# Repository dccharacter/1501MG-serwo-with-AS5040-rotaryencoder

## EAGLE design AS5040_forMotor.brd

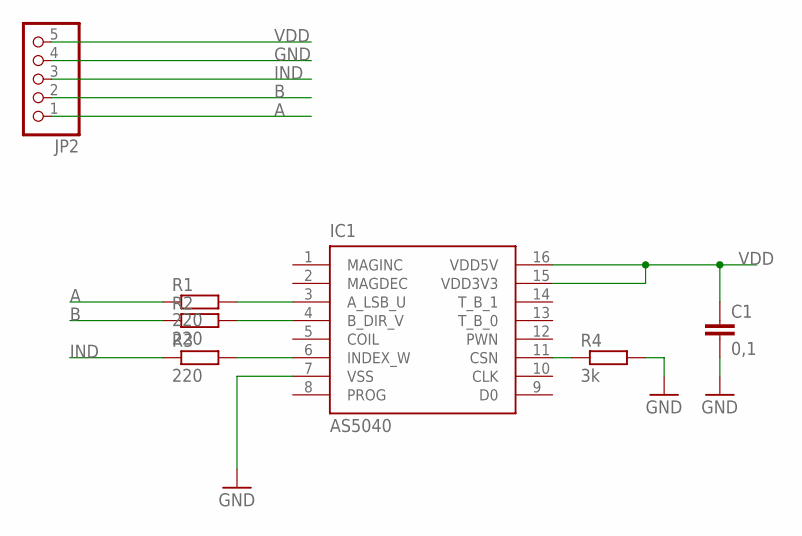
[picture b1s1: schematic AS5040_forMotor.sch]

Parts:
C1: 0,1; C0805
IC1: AS5040; SSOP16
JP2: PINHD-1X5; 1X05
R1, R2, R3: 220; M0805
R4: 3k; M0805

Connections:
A: JP2.1, R1.1
B: JP2.2, R2.1
GND: C1.2, IC1.7 (VSS), JP2.4, R4.2
IND: JP2.3, R3.1
unnamed: IC1.6 (INDEX_W), R3.2
unnamed: IC1.3 (A_LSB_U), R1.2
unnamed: IC1.4 (B_DIR_V), R2.2
unnamed: IC1.11 (CSN), R4.1
VDD: C1.1, IC1.15 (VDD3V3), IC1.16 (VDD5V), JP2.5

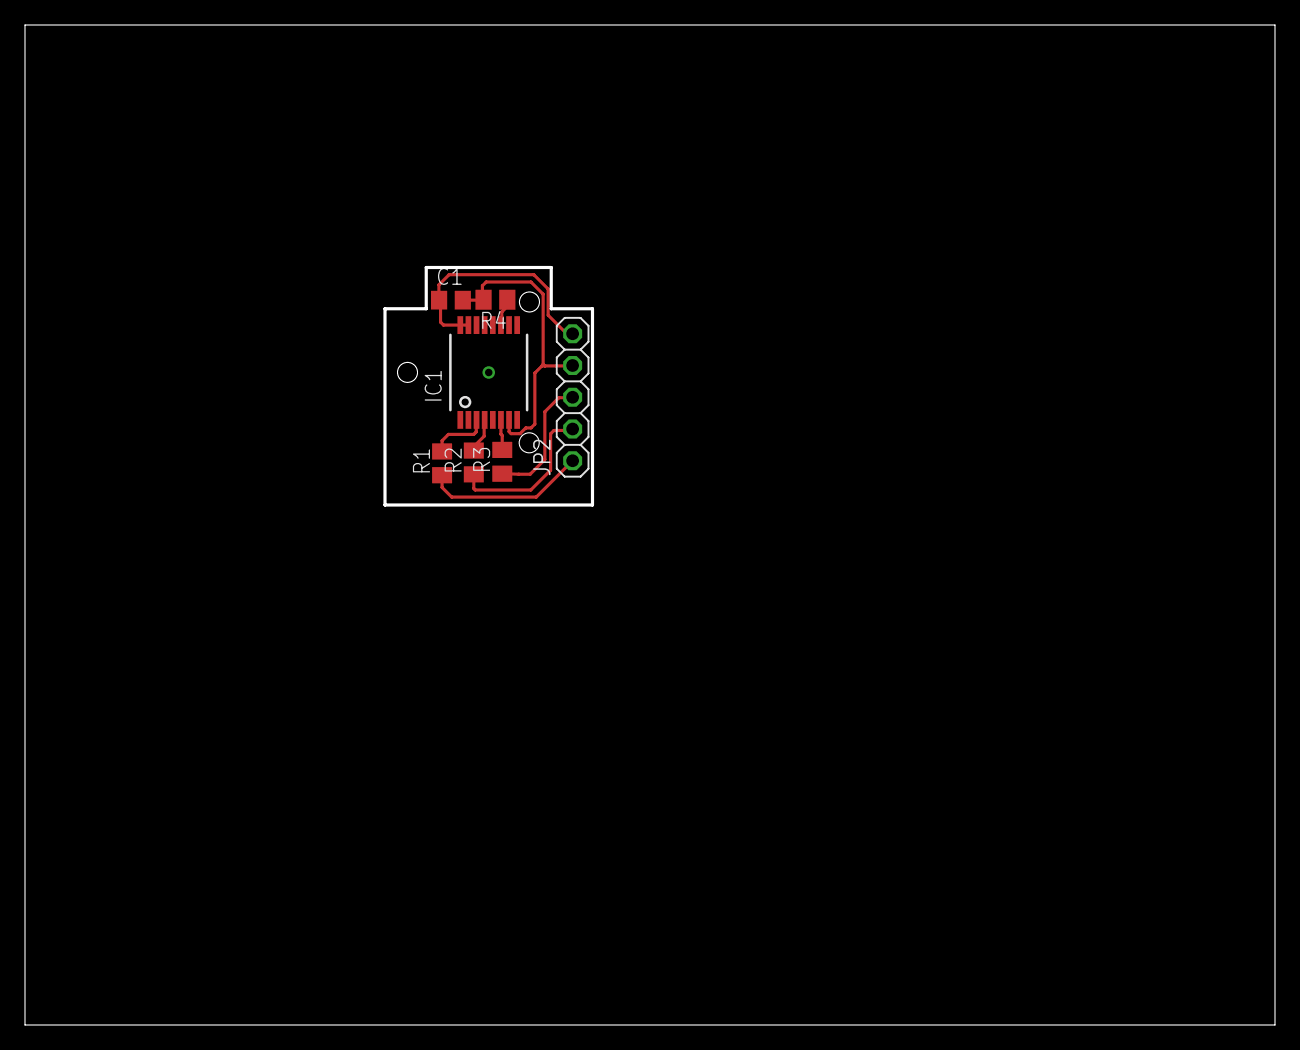
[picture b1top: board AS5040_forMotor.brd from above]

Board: 2 copper layers, 99.7 x 79.7 mm, 7 parts (0 on the bottom side), 9 nets.

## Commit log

2012-06-30 to make files available
